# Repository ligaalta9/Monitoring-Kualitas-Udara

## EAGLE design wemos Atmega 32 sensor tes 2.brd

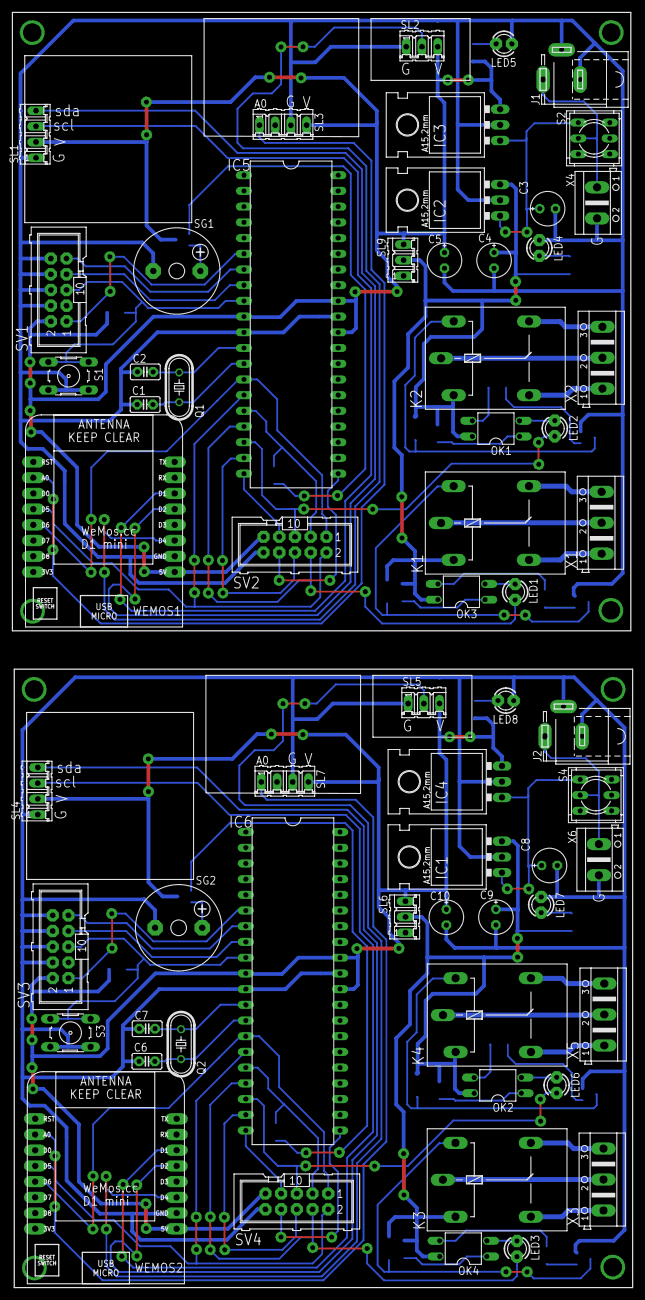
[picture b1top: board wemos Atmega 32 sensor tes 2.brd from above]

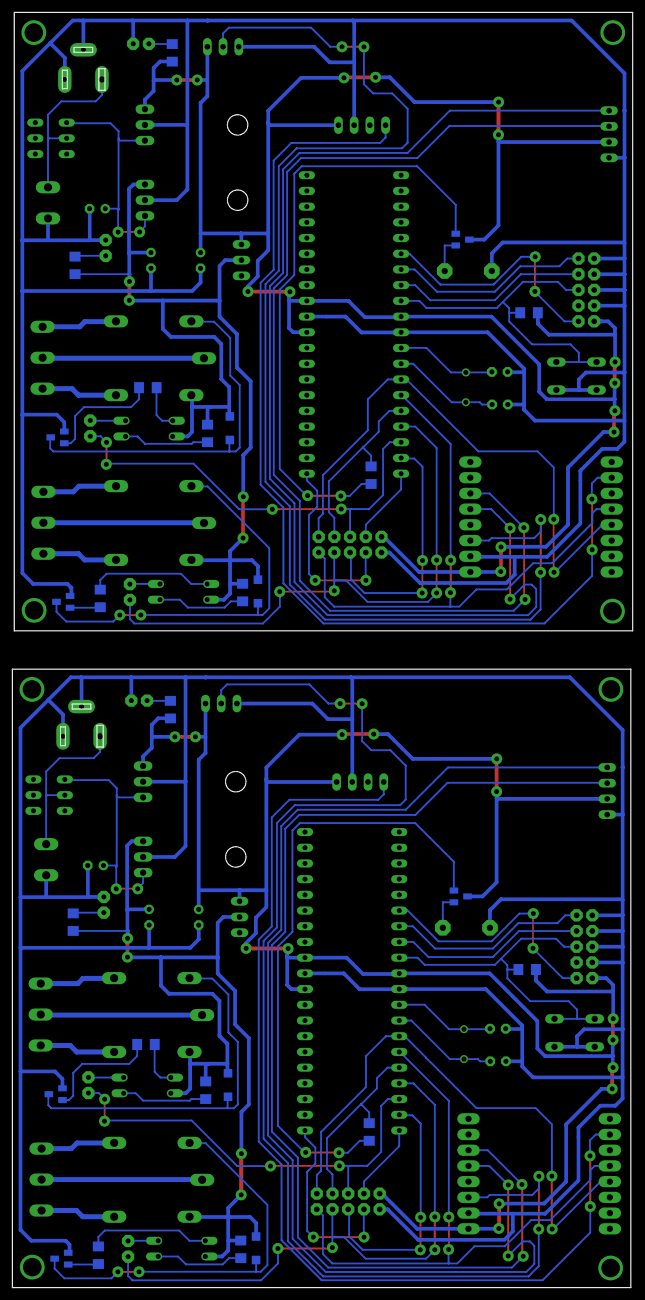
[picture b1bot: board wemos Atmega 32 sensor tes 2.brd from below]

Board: 2 copper layers, 100.3 x 206.2 mm, 88 parts (26 on the bottom side), 86 nets.

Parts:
C1, C2, C6, C7: 22PF; C2.5-2
C3, C4, C5, C8, C9, C10: 100uF/16V; E2,5-6E
D1, D2, D3, D4: 1N4148; SOD123
IC1, IC2, IC3, IC4: L7805; 78XXL
IC5, IC6: MEGA32-P; DIL40
J1, J2: VIN 6-12VDC; SPC4078
K1, K2, K3, K4: G5L; G5LE
LED1, LED2, LED3, LED4, LED5, LED6, LED7, LED8: RED; LED3MM
OK1, OK2, OK3, OK4: DIL04
Q1, Q2: 16MHZ; HC49/S
R1, R4: 10K; R1206
R2, R3, R5, R6, R7, R8, R9, R10, R11, R12, R13, R14, R15, R18: 1K; R1206
S1, S3: RESET; B3F-10XX
S2, S4: POWER ON/OFF; 9077-2
SG1, SG2: BUZZER; F/CM12P
SL1, SL4: I2C; 04P
SL2, SL5: DHT22; 03P
SL3, SL7: MQ135; 04P
SL6, SL9: SWITCH POWER; 03P
SV1, SV3: ISP PORT; ML10
SV2, SV4: PORTD; ML10
T1, T2, T4, T5: -; SOT23-BEC
T3, T6: C9013; SOT23-BEC
WEMOS1, WEMOS2: D1 MINI; WEMOS-D1-MINI
X1, X2, X3, X5: OUT; AK500/3
X4, X6: VIN 6-12VDC; AK500/2

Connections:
5V: C5.+, IC3.OUT, IC5.10, IC5.30, IC5.32, R1.2, R7.2, SL1.2, SL2.3, SL3.4, SL9.3, SV1.2, SV2.9, T3.C, WEMOS1.5V
5V1: C10.+, IC4.OUT, IC6.10, IC6.30, IC6.32, R4.2, R13.2, SL4.2, SL5.3, SL6.3, SL7.4, SV3.2, SV4.9, T6.C, WEMOS2.5V
5VA: C4.+, D1.C, D2.C, IC2.OUT, K1.1, K2.1, OK1.4, OK3.4, R2.1, R6.2, R8.1, SL9.2
5VA1: C9.+, D3.C, D4.C, IC1.OUT, K3.1, K4.1, OK2.4, OK4.4, R10.1, R12.2, R14.1, SL6.2
A0: SL3.1, WEMOS1.A0
A1: SL7.1, WEMOS2.A0
D1: SL1.3, WEMOS1.D1
D2: SL1.4, WEMOS1.D2
D3: SL4.3, WEMOS2.D1
D4: SL2.2, WEMOS1.D4
D5: SL4.4, WEMOS2.D2
D6: SL5.2, WEMOS2.D4
GND: C1.1, C2.1, C3.-, C4.-, C5.-, IC2.GND, IC3.GND, IC5.11, IC5.31, J1.1, J1.2, LED4.K, LED5.K, S1.3, S1.4, SG1.-, SL1.1, SL2.1, SL3.3, SV1.4, SV1.6, SV1.8, SV1.10, SV2.10, T1.E, T2.E, WEMOS1.GND, X4.2
GND1: C6.1, C7.1, C8.-, C9.-, C10.-, IC1.GND, IC4.GND, IC6.11, IC6.31, J2.1, J2.2, LED7.K, LED8.K, S3.3, S3.4, SG2.-, SL4.1, SL5.1, SL7.3, SV3.4, SV3.6, SV3.8, SV3.10, SV4.10, T4.E, T5.E, WEMOS2.GND, X6.2
MISO: IC5.7, SV1.9
MISO1: IC6.7, SV3.9
MOSI: IC5.6, SV1.1
MOSI1: IC6.6, SV3.1
unnamed: J1.3, S2.2, X4.1
unnamed: C3.+, IC2.IN, IC3.IN, S2.3
unnamed: C2.2, IC5.12, Q1.2
unnamed: LED4.A, R6.1
unnamed: LED5.A, R7.1
unnamed: C1.2, IC5.13, Q1.1
unnamed: R18.2, T3.B
unnamed: J2.3, S4.2, X6.1
unnamed: C8.+, IC1.IN, IC4.IN, S4.3
unnamed: SG1.+, T3.E
unnamed: LED7.A, R12.1
unnamed: LED8.A, R13.1
unnamed: R5.2, T6.B
unnamed: OK3.1, R8.2
unnamed: LED1.A, OK3.2
unnamed: SG2.+, T6.E
unnamed: OK4.1, R14.2
unnamed: OK3.3, R9.1
unnamed: R9.2, T1.B
unnamed: LED3.A, OK4.2
unnamed: D1.A, K1.2, T1.C
unnamed: OK4.3, R15.1
unnamed: D2.A, K2.2, T2.C
unnamed: R15.2, T4.B
unnamed: R3.2, T2.B
unnamed: OK1.3, R3.1
unnamed: OK1.1, R2.2
unnamed: LED2.A, OK1.2
unnamed: D3.A, K3.2, T4.C
unnamed: K2.P, X2.2
unnamed: K2.O, X2.3
unnamed: K2.S, X2.1
unnamed: K1.O, X1.3
unnamed: K1.S, X1.1
unnamed: K1.P, X1.2
unnamed: D4.A, K4.2, T5.C
unnamed: R11.2, T5.B
unnamed: OK2.3, R11.1
unnamed: OK2.1, R10.2
unnamed: LED6.A, OK2.2
unnamed: K4.P, X5.2
unnamed: K4.O, X5.3
unnamed: K4.S, X5.1
unnamed: K3.O, X3.3
unnamed: K3.S, X3.1
unnamed: K3.P, X3.2
unnamed: C7.2, IC6.12, Q2.2
unnamed: C6.2, IC6.13, Q2.1
PD0: IC5.14, SV2.1, WEMOS1.D6
PD1: IC5.15, SV2.2, WEMOS1.D5
PD2: IC5.16, R18.1, SV2.3
PD3: IC5.17, LED1.K, SV2.4
PD4: IC5.18, LED2.K, SV2.5
PD5: IC5.19, SV2.6
PD6: IC5.20, SV2.7
PD7: IC5.21, SV2.8
PD8: IC6.18, LED6.K, SV4.5
PD9: IC6.17, LED3.K, SV4.4
PD10: IC6.16, R5.1, SV4.3
PD11: IC6.14, SV4.1, WEMOS2.D6
PD12: IC6.15, SV4.2, WEMOS2.D5
PD13: IC6.19, SV4.6
PD14: IC6.20, SV4.7
PD15: IC6.21, SV4.8
RST: IC5.9, R1.1, S1.1, S1.2, SV1.5
RST1: IC6.9, R4.1, S3.1, S3.2, SV3.5
SCK: IC5.8, SV1.7
SCK1: IC6.8, SV3.7

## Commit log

2026-04-02 Add files via upload
    Monitoring Kualitas udara Wemos d1 mini + Atmega32 + aplikasi Blynk
